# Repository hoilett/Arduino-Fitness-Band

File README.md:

# Arduino-Fitness-Band
Fitness band utilizing the MAX30100 Integrated heart rate monitor and pulse oximeter from Maxim Integrated

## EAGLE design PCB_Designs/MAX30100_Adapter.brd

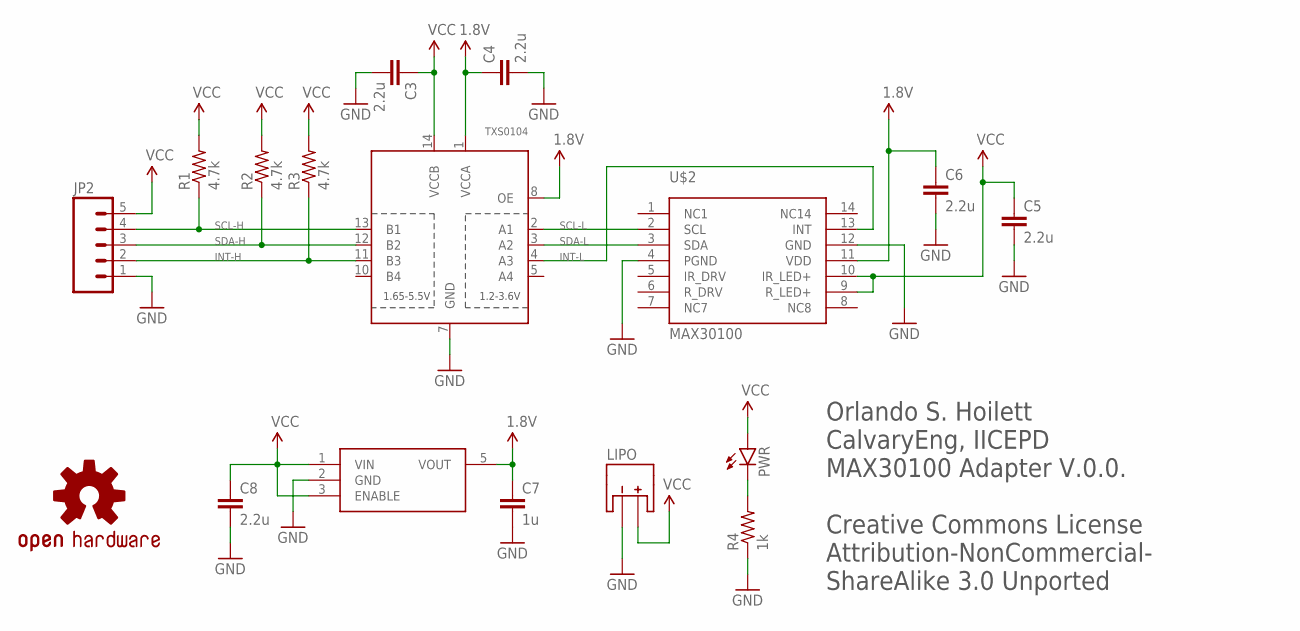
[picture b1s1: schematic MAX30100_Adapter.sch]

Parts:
C3, C4, C5, C6, C8: 2.2u; C0402
C7: 1u; C0402
JP2: M05NO_SILK; 1X05_NO_SILK
LDO: MIC5504; SOT23-5
LIPO: JST-PTH; JST-2-PTH-VERT
LOGO1: OSHW-LOGOS; OSHW-LOGO-S
PWR: LED0603; LED-0603
R1, R2, R3: 4.7k; R0402
R4: 1k; R0402
TXS0104: TXB0104PWR; TSSOP14
U$2: MAX30100; OESIP14

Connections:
1.8V: C4.1, C6.1, C7.1, LDO.5 (VOUT), TXS0104.1 (VCCA), TXS0104.8 (OE), U$2.11 (VDD)
GND: C3.2, C4.2, C5.2, C6.2, C7.2, C8.2, JP2.1, LDO.2 (GND), LIPO.-, R4.1, TXS0104.7 (GND), U$2.4 (PGND), U$2.12 (GND)
INT-H: JP2.2, R3.1, TXS0104.11 (B3)
INT-L: TXS0104.4 (A3), U$2.13 (INT)
unnamed: PWR.C, R4.2
SCL-H: JP2.4, R1.1, TXS0104.13 (B1)
SCL-L: TXS0104.2 (A1), U$2.2 (SCL)
SDA-H: JP2.3, R2.1, TXS0104.12 (B2)
SDA-L: TXS0104.3 (A2), U$2.3 (SDA)
VCC: C3.1, C5.1, C8.1, JP2.5, LDO.1 (VIN), LDO.3 (ENABLE), LIPO.+, PWR.A, R1.2, R2.2, R3.2, TXS0104.14 (VCCB), U$2.9 (R_LED+), U$2.10 (IR_LED+)

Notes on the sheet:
Orlando S. Hoilett CalvaryEng, IICEPD MAX30100 Adapter V.0.0. Creative Commons License Attribution-NonCommercial- ShareAlike 3.0 Unported

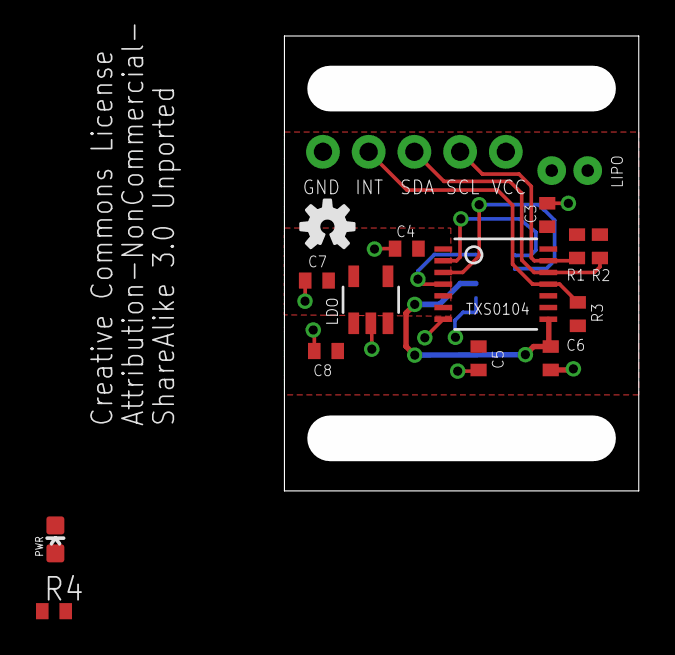
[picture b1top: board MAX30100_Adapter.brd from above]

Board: 2 copper layers, 19.7 x 25.3 mm, 17 parts (1 on the bottom side), 10 nets.

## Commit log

2016-07-10 Create LICENSE
2016-07-10 first version of PCB
2016-07-15 first version of PCB sent to OSHPark
2016-07-15 first order to OSH Park and prototype files
2016-07-15 OSH Park order 01

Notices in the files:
parts and their libraries:
SparkFun-DigitalIC: Licensing: Creative Commons ShareAlike 4.0 International - https://creativecommons.org/licenses/by-sa/4.0
